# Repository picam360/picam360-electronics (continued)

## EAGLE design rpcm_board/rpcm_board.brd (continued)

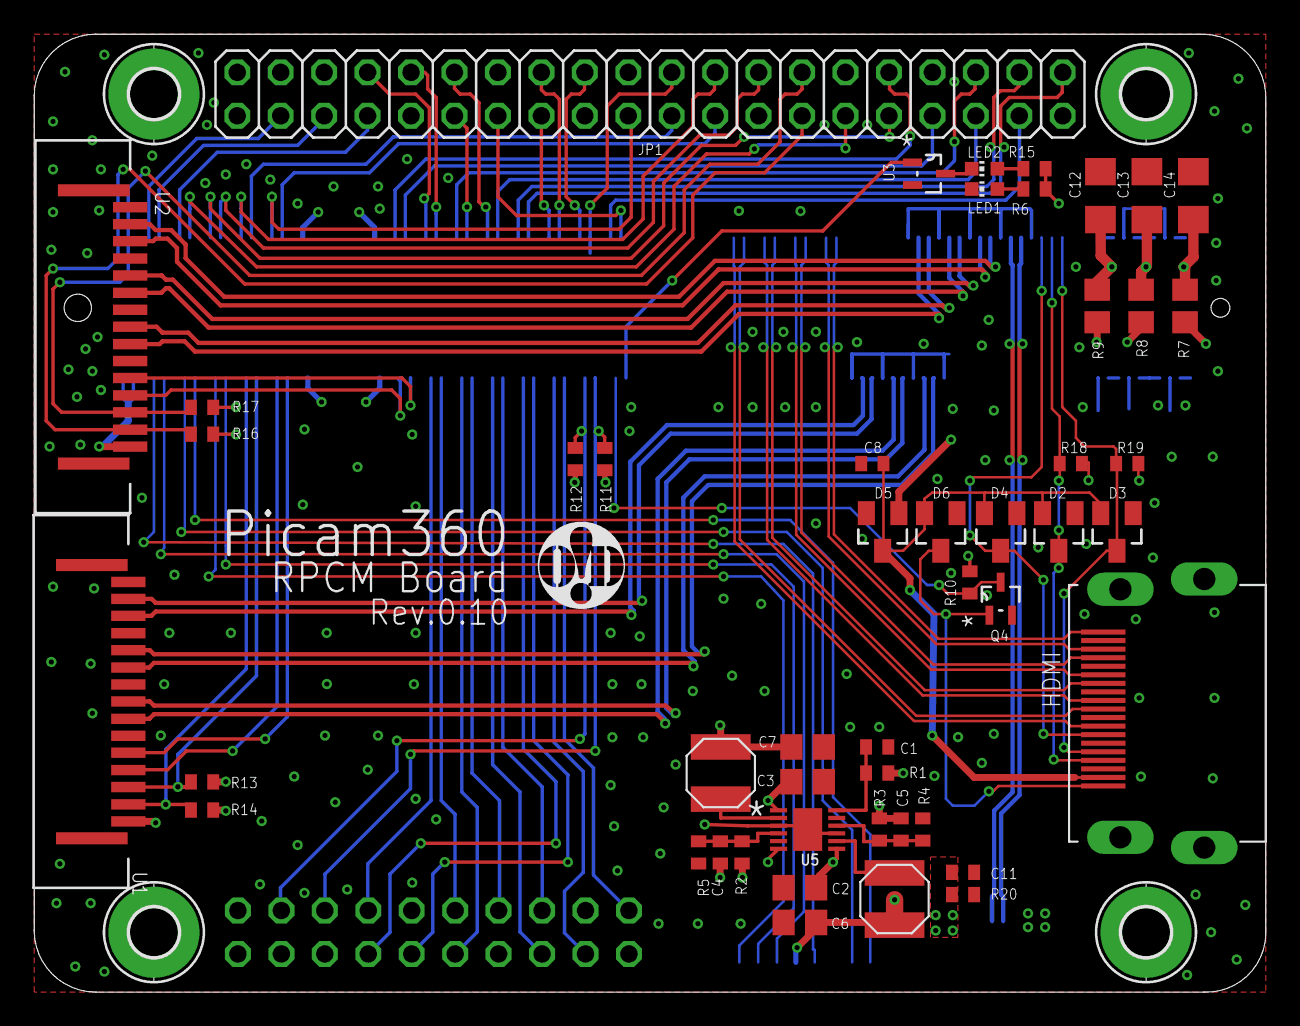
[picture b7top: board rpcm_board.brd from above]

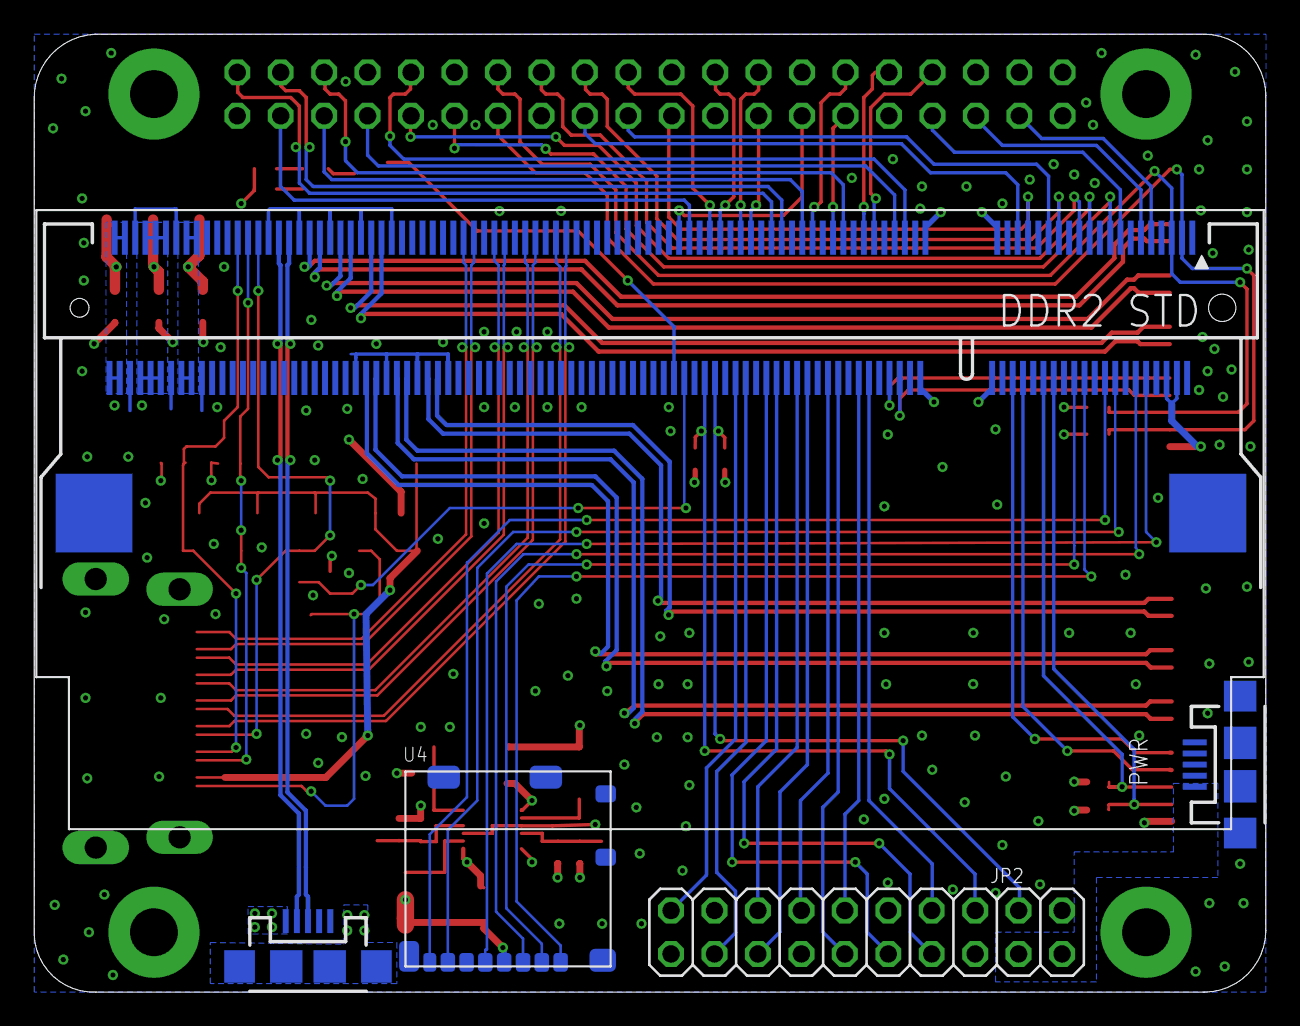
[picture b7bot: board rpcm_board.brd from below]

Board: 4 copper layers, 72.0 x 56.0 mm, 58 parts (5 on the bottom side), 97 nets.

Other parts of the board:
LOGO1: OHMYDIGIFAB_LOGO

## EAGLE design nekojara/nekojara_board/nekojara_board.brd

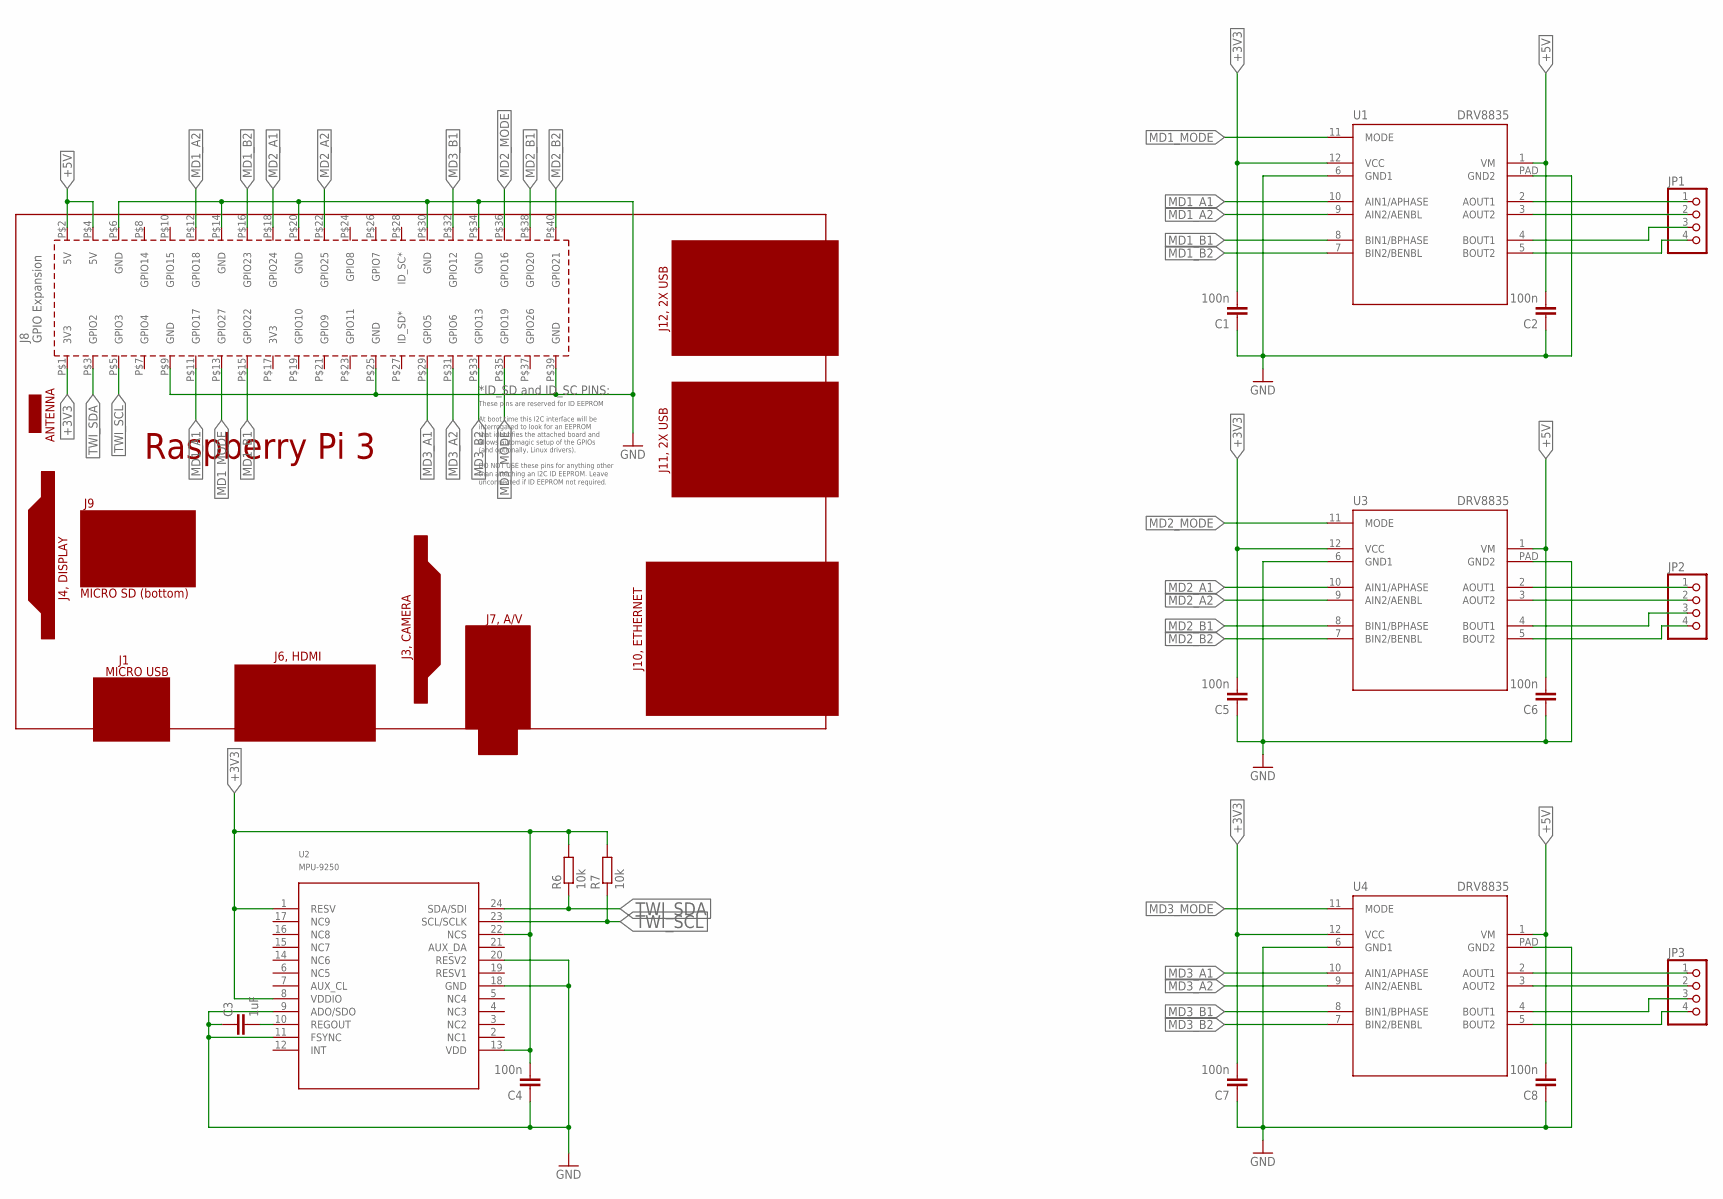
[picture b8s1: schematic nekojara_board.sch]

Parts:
C1, C2, C4, C5, C6, C7, C8: 100n; C0402
C3: 1uF; C0402
JP1, JP2, JP3: PINHD-1X4; 1X04
PCB1: RPI3
R6, R7: 10k; R0402
U1, U3, U4: DRV8835; WSON_2X3
U2: MPU-9250; LEAD-QFN24

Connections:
+3V3: C1.2, C4.2, C5.2, C7.2, PCB1.P$1 (3V3), R6.2, R7.2, U1.12 (VCC), U2.1 (RESV), U2.8 (VDDIO), U2.13 (VDD), U2.22 (NCS), U3.12 (VCC), U4.12 (VCC)
+5V: C2.2, C6.2, C8.2, PCB1.P$2 (5V), PCB1.P$4 (5V), U1.1 (VM), U3.1 (VM), U4.1 (VM)
GND: C1.1, C2.1, C3.1, C4.1, C5.1, C6.1, C7.1, C8.1, PCB1.P$6 (GND), PCB1.P$9 (GND), PCB1.P$14 (GND), PCB1.P$20 (GND), PCB1.P$25 (GND), PCB1.P$30 (GND), PCB1.P$34 (GND), PCB1.P$39 (GND), U1.6 (GND1), U1.PAD (GND2), U2.9 (ADO/SDO), U2.11 (FSYNC), U2.18 (GND), U2.20 (RESV2), U3.6 (GND1), U3.PAD (GND2), U4.6 (GND1), U4.PAD (GND2)
MD1_A1: PCB1.P$11 (GPIO17), U1.10 (AIN1/APHASE)
MD1_A2: PCB1.P$12 (GPIO18), U1.9 (AIN2/AENBL)
MD1_B1: PCB1.P$15 (GPIO22), U1.8 (BIN1/BPHASE)
MD1_B2: PCB1.P$16 (GPIO23), U1.7 (BIN2/BENBL)
MD1_MODE: PCB1.P$13 (GPIO27), U1.11 (MODE)
MD2_A1: PCB1.P$18 (GPIO24), U3.10 (AIN1/APHASE)
MD2_A2: PCB1.P$22 (GPIO25), U3.9 (AIN2/AENBL)
MD2_B1: PCB1.P$38 (GPIO20), U3.8 (BIN1/BPHASE)
MD2_B2: PCB1.P$40 (GPIO21), U3.7 (BIN2/BENBL)
MD2_MODE: PCB1.P$36 (GPIO16), U3.11 (MODE)
MD3_A1: PCB1.P$29 (GPIO5), U4.10 (AIN1/APHASE)
MD3_A2: PCB1.P$31 (GPIO6), U4.9 (AIN2/AENBL)
MD3_B1: PCB1.P$32 (GPIO12), U4.8 (BIN1/BPHASE)
MD3_B2: PCB1.P$33 (GPIO13), U4.7 (BIN2/BENBL)
MD3_MODE: PCB1.P$35 (GPIO19), U4.11 (MODE)
unnamed: JP1.1, U1.2 (AOUT1)
unnamed: JP1.2, U1.3 (AOUT2)
unnamed: JP1.3, U1.4 (BOUT1)
unnamed: JP1.4, U1.5 (BOUT2)
unnamed: JP2.1, U3.2 (AOUT1)
unnamed: JP2.2, U3.3 (AOUT2)
unnamed: JP2.3, U3.4 (BOUT1)
unnamed: JP2.4, U3.5 (BOUT2)
unnamed: JP3.1, U4.2 (AOUT1)
unnamed: JP3.2, U4.3 (AOUT2)
unnamed: JP3.3, U4.4 (BOUT1)
unnamed: JP3.4, U4.5 (BOUT2)
REGOUT: C3.2, U2.10 (REGOUT)
TWI_SCL: PCB1.P$5 (GPIO3), R7.1, U2.23 (SCL/SCLK)
TWI_SDA: PCB1.P$3 (GPIO2), R6.1, U2.24 (SDA/SDI)

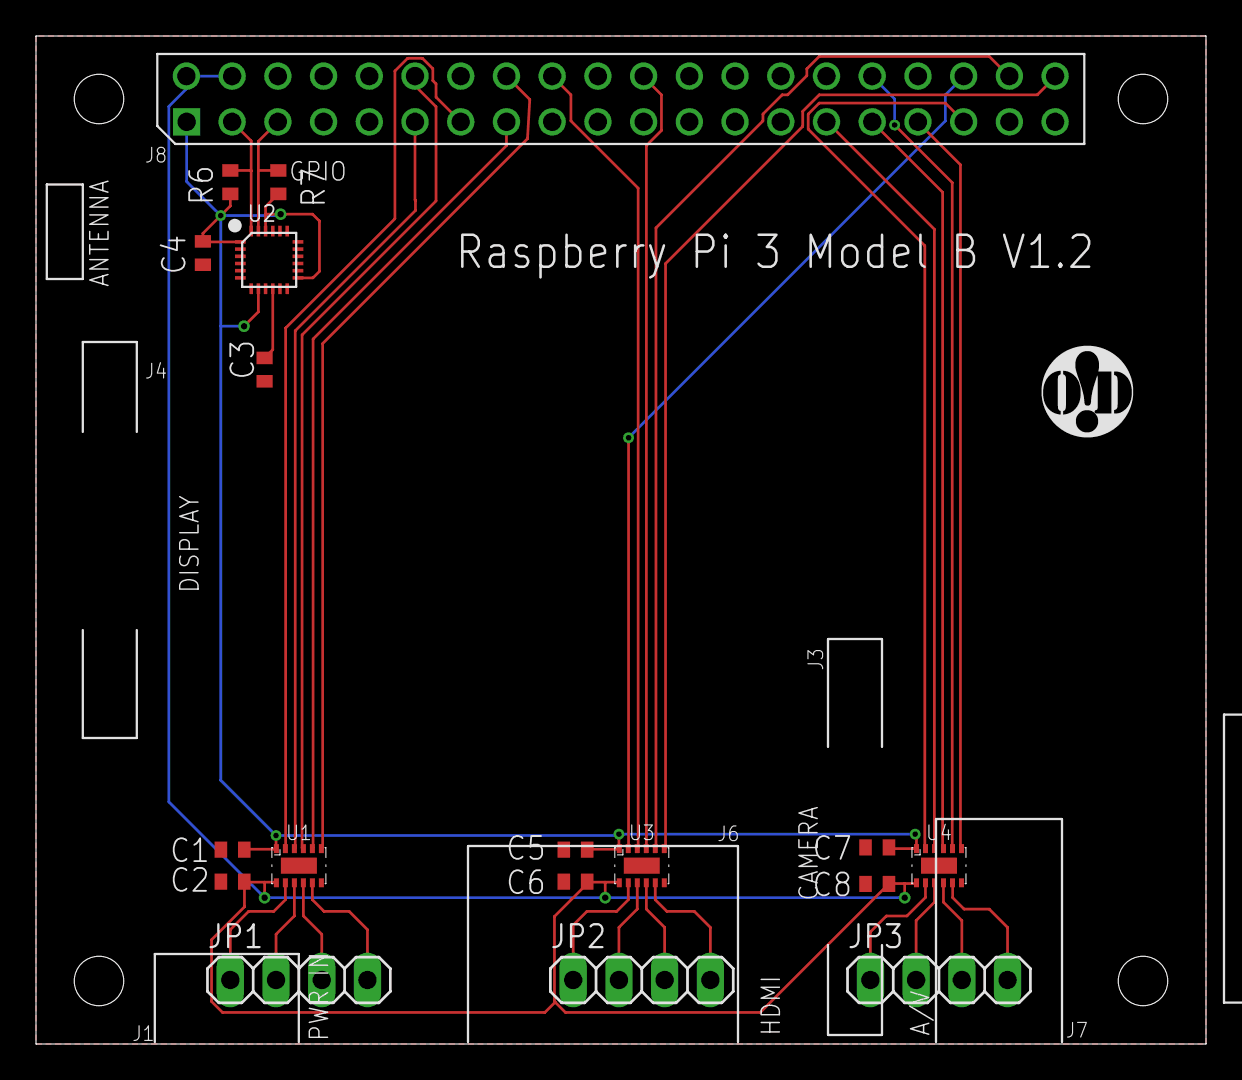
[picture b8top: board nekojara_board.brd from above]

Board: 2 copper layers, 65.0 x 56.0 mm, 19 parts (0 on the bottom side), 33 nets.

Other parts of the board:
U$1: OHMYDIGIFAB_LOGO

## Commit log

2016-05-05 picam360
2016-05-05 new camera
2016-05-05 gerber
2016-05-09 interface board update
2016-06-29 driver board 0.3 not completed
2016-06-30 driver board 0.3
2016-07-01 interface board
2017-01-16 refactoring
2017-01-16 interface_board provisional wiring
2017-01-18 for 2017 version
2017-01-18 for 2017 first version
2017-01-20 camera_unit
2017-01-20 after order
2017-01-21 tune +5V
2017-02-09 before hdmi
2017-02-09 after hdmi
2017-02-10 before autorouter
2017-02-10 before order
2017-02-11 add camera_unit.sch
2017-02-14 hdmi
2017-02-20 camera_unit 0.3
2017-02-20 rpcm 0.8+
2017-02-21 camera_unit, camera_adapter
2017-05-02 usb ext board
2017-05-02 debug
2017-05-06 interface board 0.7 rpcm board 0.10
2017-05-06 gerber file
2017-05-06 *.scr
2017-05-16 after test
2017-12-11 nekojara
2017-12-11 usb_ext_board_21mm
2017-12-11 tune value
2017-12-11 revert to 2.7mm hole for camera
2018-02-26 slipring
2018-03-06 nekojara : usb
2018-04-10 rename to ugv
2018-04-11 ugv : before v1.0
2018-04-11 ugv : production
2018-06-02 before ugv v1
2018-11-28 usb_50w
2018-12-07 usv50w
2018-12-26 usv_50w
2019-03-26 tricle charger
2019-03-26 usv 50w rev0.2
2019-04-11 usv 50w 0.3
